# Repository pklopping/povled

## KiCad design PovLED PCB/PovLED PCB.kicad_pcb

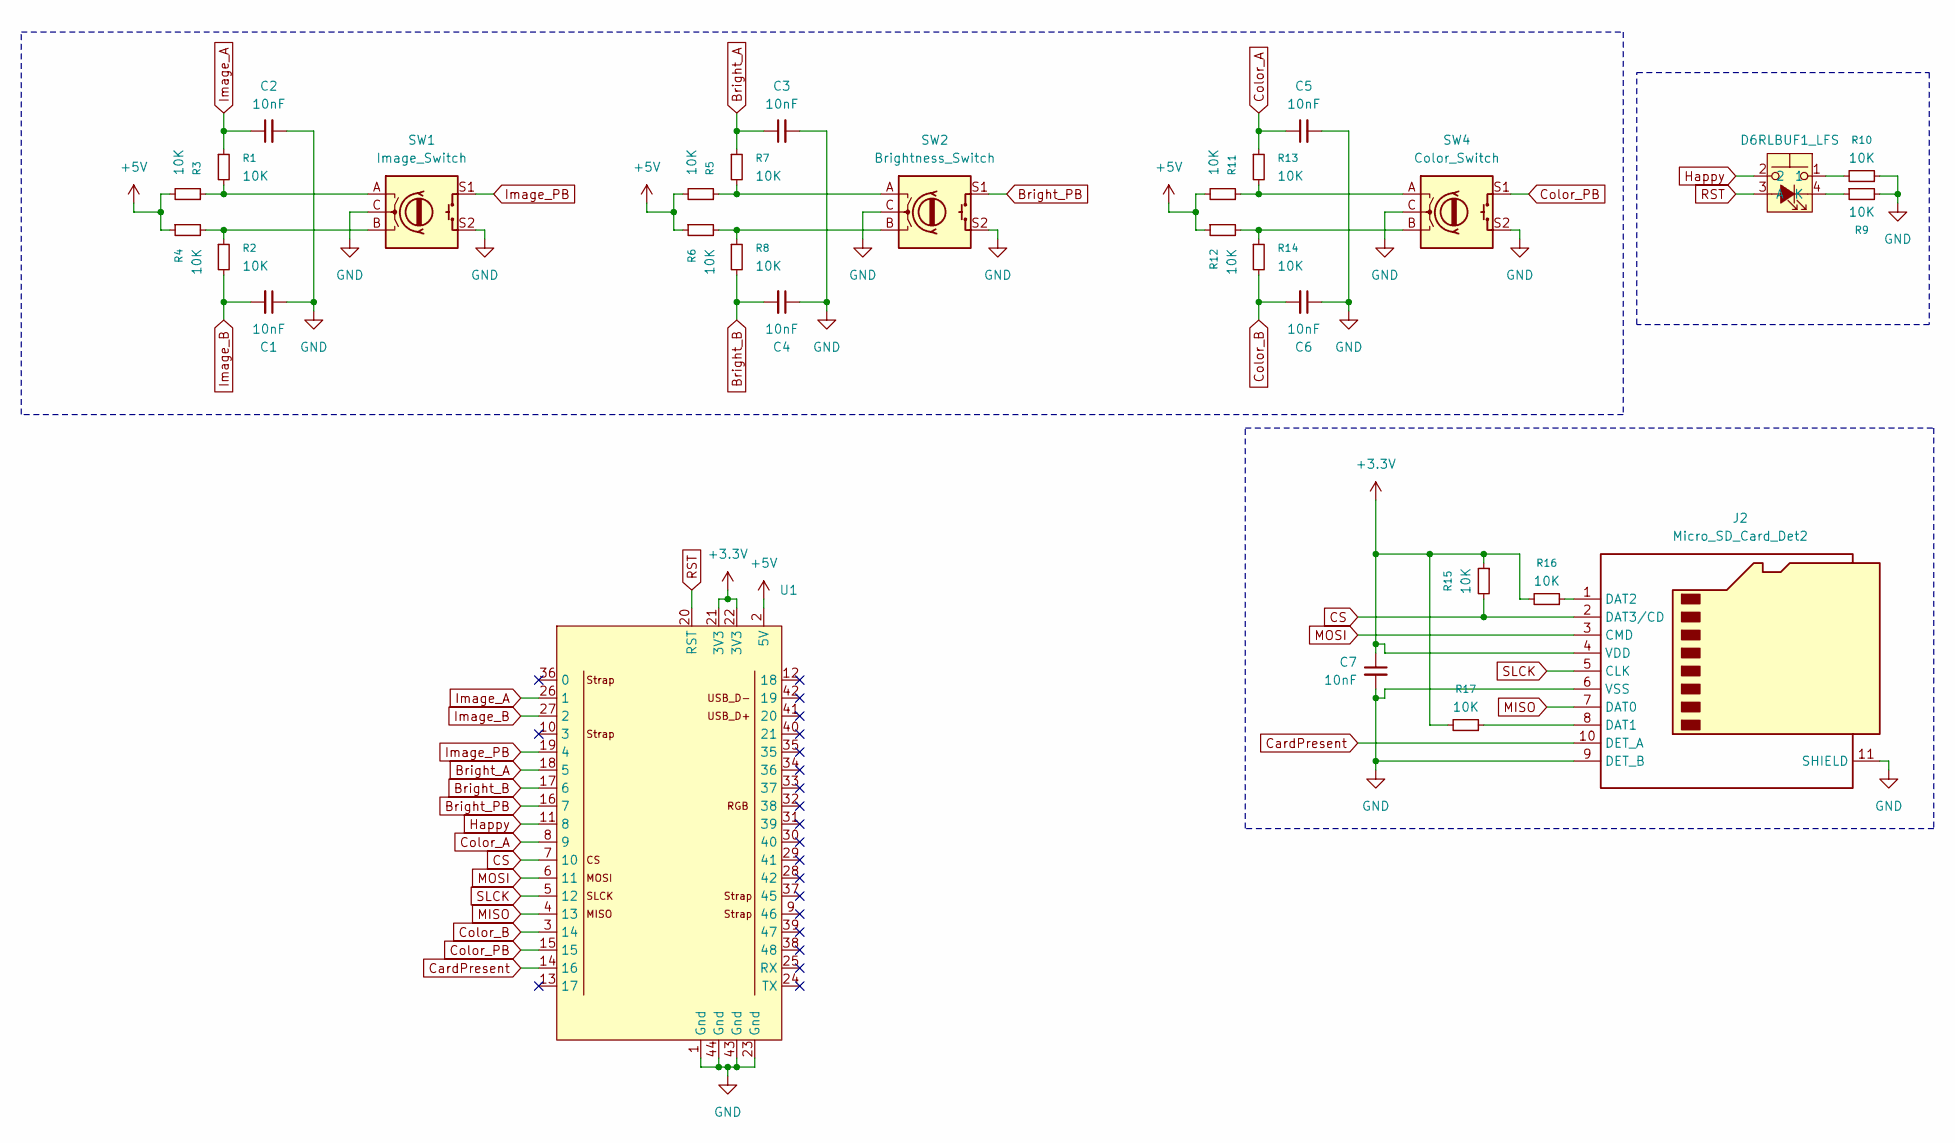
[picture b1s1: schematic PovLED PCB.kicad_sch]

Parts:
C1, C2, C3, C4, C5, C6, C7: 10nF; C_0805_2012Metric
J2: Micro_SD_Card_Det2; microSD_HC_Molex_104031-0811
R1, R2, R3, R4, R5, R6, R7, R8, R9, R10, R11, R12, R13, R14, R15, R16, R17: 10K; R_0805_2012Metric
S1: D6RLBUF1_LFS; D6RLBUF1LFS; Mouser Part Number 611-D6RLBUF1LFS
SW1: Image_Switch; RotaryEncoder_Bourns_Vertical_PEC12R-3x17F-Sxxxx
SW2: Brightness_Switch; RotaryEncoder_Bourns_Vertical_PEC12R-3x17F-Sxxxx
SW4: Color_Switch; RotaryEncoder_Bourns_Vertical_PEC12R-3x17F-Sxxxx
U1: ESP32-S3-DevKitC-1-N8R8

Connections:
+3.3V: C7.1, J2.4 (VDD), R15.1, R16.2, R17.2, U1.21 (3V3), U1.22 (3V3)
+5V: R3.2, R4.1, R5.2, R6.1, R11.2, R12.1, U1.2 (5V)
Bright_A: C3.1, R7.1, U1.18 (5)
Bright_B: C4.2, R8.2, U1.17 (6)
Bright_PB: SW2.S1, U1.16 (7)
CS: J2.2 (DAT3/CD), R15.2, U1.7 (10)
CardPresent: J2.10 (DET_A), U1.14 (16)
Color_A: C5.1, R13.1, U1.8 (9)
Color_B: C6.2, R14.2, U1.3 (14)
Color_PB: SW4.S1, U1.15
GND: C1.1, C2.2, C3.2, C4.1, C5.2, C6.1, C7.2, J2.6 (VSS), J2.9 (DET_B), J2.11 (SHIELD), R9.2, R10.1, SW1.C, SW1.S2, SW2.C, SW2.S2, SW4.C, SW4.S2, U1.1 (Gnd), U1.23 (Gnd), U1.43 (Gnd), U1.44 (Gnd)
Happy: S1.2, U1.11 (8)
Image_A: C2.1, R1.1, U1.26 (1)
Image_B: C1.2, R2.2, U1.27 (2)
Image_PB: SW1.S1, U1.19 (4)
MISO: J2.7 (DAT0), U1.4 (13)
MOSI: J2.3 (CMD), U1.6 (11)
unnamed: J2.8 (DAT1), R17.1
unnamed: J2.1 (DAT2), R16.1
unnamed: R1.2, R3.1, SW1.A
unnamed: R2.1, R4.2, SW1.B
unnamed: R5.1, R7.2, SW2.A
unnamed: R6.2, R8.1, SW2.B
unnamed: R10.2, S1.1
unnamed: R11.1, R13.2, SW4.A
unnamed: R12.2, R14.1, SW4.B
unnamed: R9.1, S1.4 (K)
RST: S1.3 (A), U1.20 (RST)
SLCK: J2.5 (CLK), U1.5 (12)

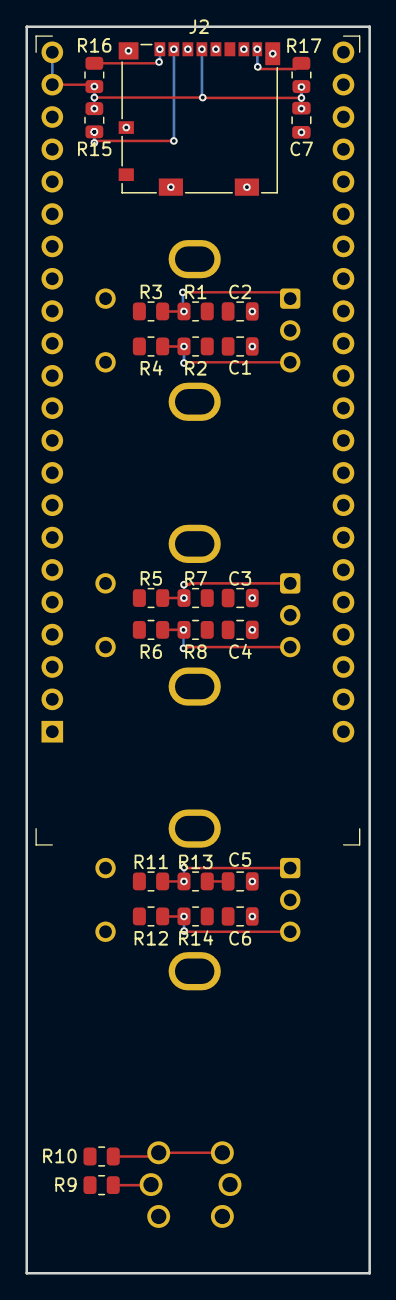
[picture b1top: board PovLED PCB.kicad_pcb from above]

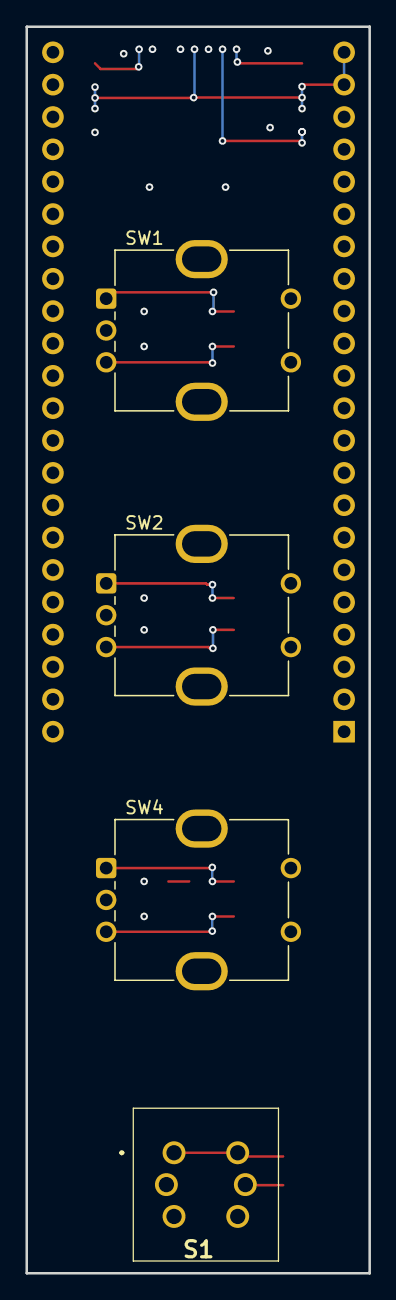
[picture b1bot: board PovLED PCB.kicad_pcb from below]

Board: 2 copper layers, 26.9 x 97.9 mm, 30 parts (4 on the bottom side), 29 nets.

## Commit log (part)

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2023-10-08 Switching to a mega and single bits per pixel, still too slow
2023-10-08 Switched to Teensy 4.1. Much better
2023-10-08 Hooray!
2023-10-08 Found the color order
2023-10-10 testing out memmove
2023-10-10 Adding an FPS counter
2023-10-10 Let's blind everyone
2023-10-10 Commenting out the frame counter to avoid blinks
2023-12-17 Adding tree
2024-02-03 heart
2024-02-15 new hat
2024-02-15 more images
2024-02-15 Fixed the color order. I think
2024-03-18 easter
2024-10-04 re-fixing color order
2024-10-04 color orders are dumb, this is still broken
2025-05-30 Whoops, it's been a minute since I checked in
2025-12-20 WOrking on custom PCB to add features
2025-12-20 I need to add a gitignore
2025-12-22 PCB stuff
2025-12-22 Implementing .gitignore
2025-12-22 Adding models
2025-12-22 encoder models
2025-12-22 knobs
2025-12-29 Beginning layout
